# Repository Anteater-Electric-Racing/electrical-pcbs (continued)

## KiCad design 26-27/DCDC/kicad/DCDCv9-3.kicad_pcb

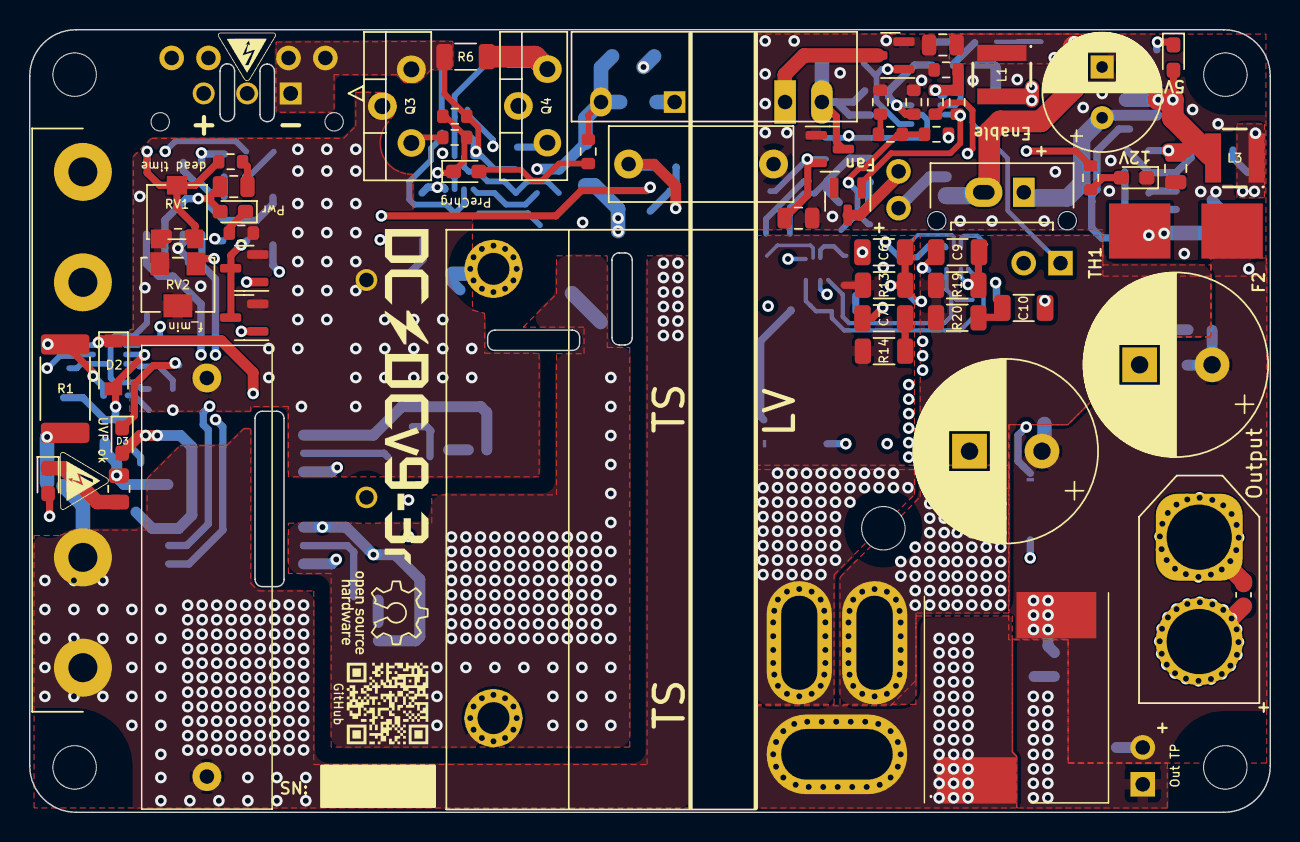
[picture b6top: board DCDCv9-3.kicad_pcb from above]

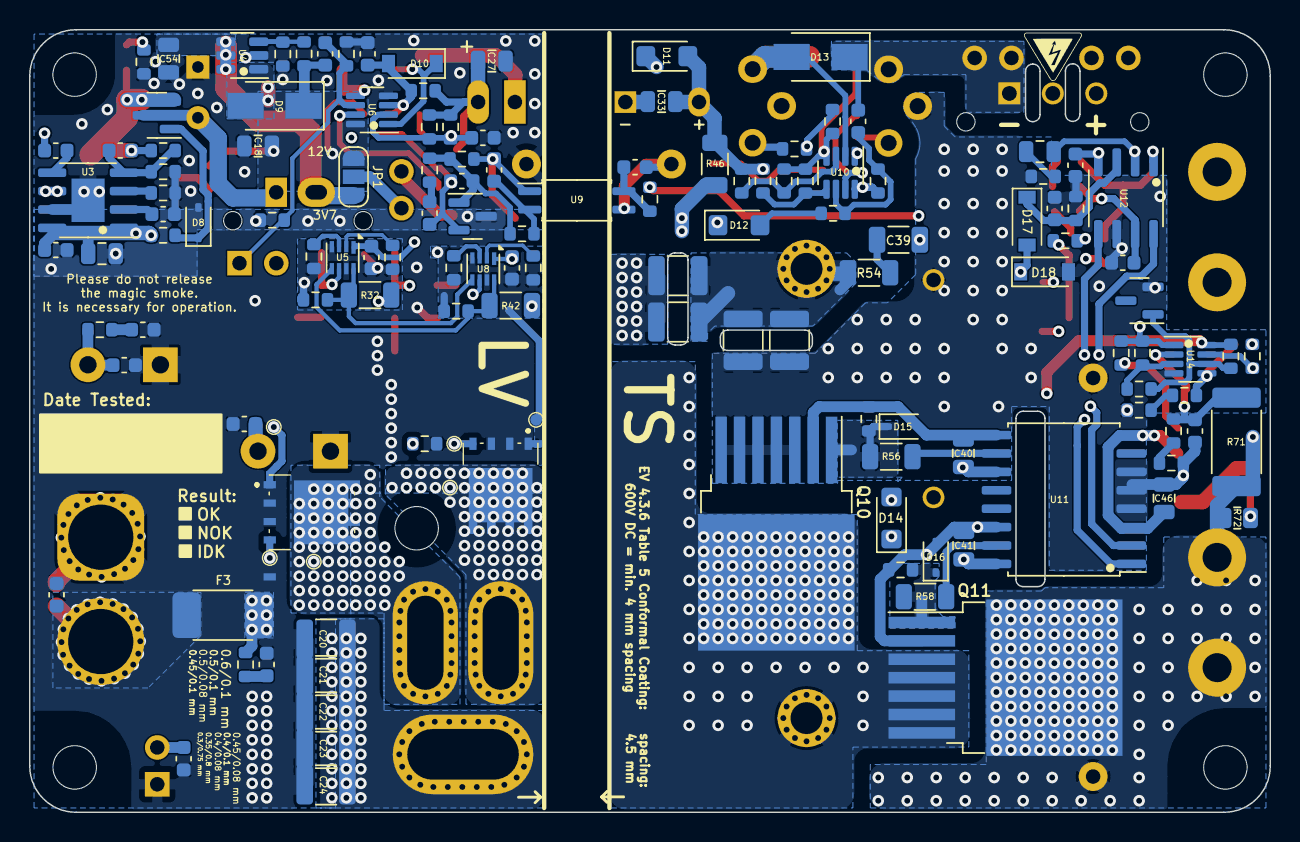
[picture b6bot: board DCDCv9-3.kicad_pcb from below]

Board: 4 copper layers, 85.6 x 54.0 mm, 208 parts (140 on the bottom side), 102 nets.

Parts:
C1: 2uF; MKP1848520704K2
C2, C15, C40, C41: 2.2uF; C_0805_2012Metric
C3: 22nF; R76UI22205050J
C4: 3.3nF; C_Disc_D12.5mm_W5.0mm_P10.00mm
C5, C33, C46: 10uF; C_0805_2012Metric
C6, C9: 1 nF; C_1206_3216Metric
C7, C10, C39: 470pF; C_1206_3216Metric
C8, C12, C18, C27, C42, C54: 22uF; C_0805_2012Metric
C11, C13: 2200uF; CP_Radial_D12.5mm_P5.00mm_symbol_inside
C14, C28: 100nF; C_0603_1608Metric
C16, C49, C50, C51, C52, C53, C55, C56, C57: 1nF; C_0603_1608Metric
C17, C19, C25, C31, C45: 1uF; C_0603_1608Metric
C20, C21, C22, C23, C24: 10uF; C_1210_3225Metric
C26, C44, C47: 22nF; C_0603_1608Metric
C29: 47pF; C_0603_1608Metric
C30, C32, C48: 10nF; C_0603_1608Metric
C34, C35, C36, C37: 5.6nF; C_1210_3225Metric
C38: 120pF; C_0603_1608Metric
C43: 470nF; C_0603_1608Metric
C_start1: 3.8V 25F Supercap; CP_Radial_D8.0mm_P3.50mm
D1: HV_Orange; LED_0603_1608Metric_Pad1.05x0.95mm_HandSolder
D2, D10, D17, D18: 1N4448; D_SOD-123
D3, D4, D5, D6, D7: Green; LED_0603_1608Metric_Pad1.05x0.95mm_HandSolder
D8, D15, D16: CDSOD323-T12; D_SOD-323
D9, D13: SS1H10; D_SMA
D11, D12, D14: VS-E7FX0212-M3/I; D_SMF
F1: 1.6A; Fuseholder0,25Zoll_32mm_littlefuse_102_122
F2: 500mA; NANO-0154-OMNI-BLOK-Fuse-Holder
F3: 20A; Bel_SMCF_Fuse_2410_6125Metric
HV_Logo_1, HV_Logo_1#2, HV_Logo_1#3: HV_Logo_1; HV_Logo_small
J1: 43650-0315; 43650-03YY_151617
J2, J4, J6, J7, J8: Conn_01x02_Male; PinHeader_1x02_P2.54mm_Vertical
J3: Conn_01x02; Molex_Micro-Fit_3.0_43650-0215_1x02_P3.00mm_Vertical_combin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
J5: XT60 Male; AMASS_XT60-F_1x02_P7.20mm_Vertical
JP1: Fan Voltage Select; SolderJumper-3_P1.3mm_Open_RoundedPad1.0x1.5mm_NumberLabels
L1: 4.7uH; ASPI-4030S
L2: 1uH; 7443091100_v9.2
L3: 10uH; ASPI-4030S
NT1, NT2: NetTie_2; dummy_net_line_0.5mm
Q1, Q2, Q5, Q6, Q7: PMV20ENR; SOT-23
Q3: SIHP24N80AE-GE3; TO-220-3_Vertical_HV1.2mm
Q4: IXYP8N90C3; TO-220-3_Vertical_HV1.2mm
Q8, Q9: BSC027N06LS5ATMA1
Q10, Q11: IMBG65R050M2HXTMA1; TO-263-7_TabPin8
QR_Coode_1: QR_Coode; GitHub_QR_Code
R1, R71: 100M; R_2512_6332Metric_Pad1.40x3.35mm_HandSolder
R2, R72: 330k; R_0805_2012Metric
R3: 3.0k; R_0603_1608Metric
R4, R39, R41, R59, R61: 1k; R_0603_1608Metric
R5, R7, R9, R11, R15, R16, R21, R23, R30, R33, R40, R43, R51, R52, R55, R57, R63: 10k; R_0603_1608Metric
R6, R14, R20: 47; R_1206_3216Metric
R8, R10, R22, R29, R38, R48, R49: 2.2k; R_0603_1608Metric
R12: 910; R_0603_1608Metric
R13, R19: 100; R_1206_3216Metric
R17, R24: 27k; R_0603_1608Metric
R18, R27, R50: 470k; R_0603_1608Metric
R25: 240k; R_0603_1608Metric
R26, R45, R47, R53, R67, R70, R75: 100k; R_0603_1608Metric
R28, R34, R66: 33k; R_0603_1608Metric
R31, R36: 4.7k; R_0603_1608Metric
R32, R42: 4.7; R_1206_3216Metric
R35: 330k; R_0603_1608Metric
R37: 47k; R_0603_1608Metric
R44: 510; R_0603_1608Metric
R46: 20; R_1206_3216Metric
R54: 10M; R_1206_3216Metric
R56, R58: 10; R_1206_3216Metric
R60: 82k; R_0603_1608Metric
R62, R69: 100M; R_0603_1608Metric
R64: 820k; R_0603_1608Metric
R65: 510k; R_0603_1608Metric
R68: 1.6M; R_0603_1608Metric
R73, R74: 10; R_0603_1608Metric
RV1: 20k; Potentiometer_Bourns_PVG3G
RV2: 10k; Potentiometer_Bourns_3214W_Vertical
T1: DIY Transformer ETD 39; Transformer_ETD39_uprightV3.6 (PSS 24V)
TH2: 1k PTC; R_0603_1608Metric
TP1, TP2, TP3, TP4, TP5, TP6: TestPoint; TestPoint_Pad_D0.8mm_DC-DC
TP8: GaN GND2; TestPoint_Pad_D0.8mm_DC-DC
U1: RP-1212S; Converter_DCDC_TRACO_TBA 1-1212HI-3kV-iso
U2: RT9058-90GVL; SOT-23
U3: MP4541_SOP8-EP; SOIC-8-1EP_3.9x4.9mm_P1.27mm_EP2.29x3mm XL7005
U4: TLV61048DBVR; SOT-23-6
U5, U8: NCP4305DMTTWG; WDFN-8_2x2mm_P0.5mm
U6, U10, U14: LM2904BIDDFR; SOT-23-8_DC-DC_v9
U7: TL431BCDBZR; SOT-23
U9: ACPL-217-50AE; SOIC-4_4.55x2.6mm_P1.27mm
U11: UCC21520DW; SOIC-16W_7.5x10.3mm_P1.27mm
U12: UCC25600; SOIC-8_3.9x4.9mm_P1.27mm
U13: ZXRE330ASA-7; SOT-23

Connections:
24V_TP: C11.1, C13.1, C50.2, C51.2, C52.2, F2.1, F3.1, J4.1, L2.2, R17.1, R73.1, R74.1
+3V7: C8.1, C54.1, J3.2, JP1.3 (B), L1.1, U4.4 (~SHDN), U4.5 (IN), U4.6 (nc)
+9V: C5.1, C30.2, R39.1, U2.2 (VO), U9.1
+12V_HS: C41.2, D14.1 (K), U11.16 (VDDA)
+12V_IN: C2.2, C40.2, C45.2, C46.1, D2.1 (K), D3.2 (A), D4.2 (A), D11.1 (K), R70.1, U11.3 (VCCI), U11.8 (VCCI), U11.11 (VDDB), U12.7 (VCC), U14.8 (V+)
+12V_sw: C18.1, C19.2, C25.1, C27.1, C31.1, D9.1 (K), J8.1, JP1.1 (A), R16.1, R21.2, R27.1, R34.1, R35.2, R36.2, U1.1 (+VIN), U2.3 (VI), U5.1 (VCC), U6.8 (V+), U8.1 (VCC)
+24V: C15.2, C53.2, F2.2, R26.2, U3.1 (EN), U3.8 (VIN)
+HV: C1.2, C34.1, C35.1, F1.2, Q11.8 (D), R1.1, R71.1, R72.1
+HV_in: F1.1, J1.3, J7.1, J7.2
-HV_in: C33.2, C38.1, D13.1 (K), J1.1, J6.1, J6.2, Q3.3 (S), R6.2, R7.2, R48.1, R50.1, R51.2, U1.5 (-VOUT), U10.4 (V-)
-HV_pc: C1.1, C3.2, C4.1, C32.2, C36.2, C37.2, C43.2, C44.1, C45.1, C46.2, C47.2, D12.1 (K), D18.2 (A), Q1.2 (S), Q2.2 (S), Q3.2 (D), Q4.2 (C), Q10.3 (S), Q10.4 (S), Q10.5 (S), Q10.6 (S), Q10.7 (S), R2.2, R3.2, R5.1, R59.2, R60.1, R65.2, R68.2, RV1.3, RV2.2, RV2.3, U9.3, U11.4 (GND), U11.5 (DIS), U11.6 (DT), U12.6 (GND), U13.2, U14.4 (V-)
/HB_out: Q10.8 (D), Q11.3 (S), Q11.4 (S), Q11.5 (S), Q11.6 (S), Q11.7 (S), T1.1 (AA)
/HS: U11.1 (INA), U12.8 (GD1)
/LS: U11.2 (INB), U12.5 (GD2)
/OC: C44.2, D17.1 (K), R60.2, U12.3 (OC)
/OTP_FAN: Q5.1 (G), R18.1, U6.7
/OTP_OFF: D10.1 (K), Q6.1 (G), U6.1
/OVP: Q2.1 (G), R69.1, U14.7
/Opc+: C32.1, R44.2, U9.4
/Synchronous Rectification/3: Q9.5 (D_1), Q9.6 (D_2), Q9.7 (D_3), Q9.8 (D_4), Q9.9 (D_5), R13.2, R14.1, T1.3 (SB), TP5.1
/Synchronous Rectification/5: Q8.5 (D_1), Q8.6 (D_2), Q8.7 (D_3), Q8.8 (D_4), Q8.9 (D_5), R19.2, R20.1, T1.5 (SA), TP3.1
/UVP: Q1.1 (G), R62.1, R63.1, U14.1
GND: C4.2, C5.2, C7.1, C8.2, C10.1, C11.2, C12.1, C13.2, C15.1, C17.1, C18.2, C20.2, C21.2, C22.2, C23.2, C24.2, C27.2, C28.1, C48.1, C49.1, C50.1, C51.1, C52.1, C53.1, C54.2, C55.1, C56.1, C57.1, C_start1.2 (-), D6.1 (K), D8.2 (A2), J4.2, J5.2, NT1.2, NT2.2, Q5.2 (S), Q6.2 (S), Q8.1 (S_1), Q8.2 (S_2), Q8.3 (S_3), Q9.1 (S_1), Q9.2 (S_2), Q9.3 (S_3), R10.2, R11.2, R15.1, R22.1, R23.2, R25.1, R28.2, R31.1, R75.2, TH2.2, TP8.1, U2.1 (GND), U3.7 (GND), U4.2 (GND), U6.4 (V-), U7.3 (A)
unnamed: C2.1, R4.2
unnamed: C7.2, R14.2
unnamed: C10.2, R20.2
unnamed: C26.2, R37.1
unnamed: C30.1, R41.1, U9.2
unnamed: C39.2, R54.1
unnamed: C42.2, R59.1
unnamed: C56.2, R73.2
unnamed: C57.2, R74.2
unnamed: C_start1.1 (+), J3.1, Q7.3 (D)
unnamed: D1.2 (A), R72.2
unnamed: D1.1 (K), R2.1
unnamed: C47.1, D2.2 (A), R67.2, R71.2, U14.2 (-)
unnamed: D3.1 (K), R63.2
unnamed: D4.1 (K), R5.2
unnamed: D5.2 (A), R9.1
unnamed: D5.1 (K), R7.1, R8.2, U10.7
unnamed: D6.2 (A), R21.1
unnamed: C12.2, C16.2, D7.2 (A), L3.2, Q7.2 (S), R24.1
unnamed: D7.1 (K), R22.2
unnamed: D8.1 (A1), Q7.1 (G), R26.1
unnamed: D9.2 (A), L1.2, U4.1 (SW)
unnamed: C48.2, D10.2 (A), R11.1, R34.2, U6.3 (+)
unnamed: C33.1, D11.2 (A), R9.2, R45.2, R46.2, R47.2, R53.2, U1.7 (+VOUT), U10.8 (V+)
unnamed: D12.2 (A), R52.1
unnamed: D13.2 (A), Q4.3 (E), R6.1, U10.2 (-)
unnamed: D14.2 (A), R46.1
unnamed: D15.1 (A1), Q10.1 (G), R55.1, R56.1
unnamed: C40.1, D15.2 (A2), Q10.2 (DS), R55.2, U11.9 (VSSB)
unnamed: D16.1 (A1), Q11.1 (G), R57.1, R58.1
unnamed: C41.1, D16.2 (A2), Q11.2 (DS), R57.2, U11.14 (VSSA)
unnamed: C39.1, D17.2 (A), D18.1 (K)
unnamed: J2.1, JP1.2 (C)
unnamed: J2.2, Q5.3 (D)
unnamed: C49.2, C55.2, F3.2, J5.1
unnamed: C19.1, J8.2, R31.2, R75.1, U6.6 (-)
unnamed: Q1.3 (D), Q2.3 (D), R61.1
unnamed: Q3.1 (G), R8.1
unnamed: Q4.1 (G), R49.1
unnamed: Q8.4 (G), R32.1, TP2.1
unnamed: Q9.4 (G), R42.1, TP4.1
unnamed: R10.1, R12.2
unnamed: R49.2, R51.1, U10.1
unnamed: R65.1, R66.2
unnamed: R67.1, R68.1
unnamed: C34.2, C35.2, C36.1, C37.1, R54.2, T1.2 (AB)
unnamed: C20.1, C21.1, C22.1, C23.1, C24.1, L2.1, T1.4 (SC)
unnamed: C14.2, U3.5 (BST)
unnamed: C16.1, R23.1, R24.2, U3.4 (FB)
unnamed: R25.2, U3.3 (FREQU)
unnamed: C14.1, L3.1, U3.6 (SW)
unnamed: C17.2, U3.2 (VCC)
unnamed: R27.2, R28.1, U4.3 (FB)
unnamed: C9.2, R19.1, U5.6 (CS)
unnamed: R30.2, R32.2, U5.8 (DRV), U8.5 (TRIG/DIS)
unnamed: C9.1, C25.2, NT1.1, R29.1, R30.1, R33.1, TP1.1, U5.4 (LLD), U5.7 (GND)
unnamed: R33.2, U5.2 (MIN_TOFF)
unnamed: R29.2, U5.3 (MIN_TON)
unnamed: R40.2, R42.2, U5.5 (TRIG/DIS), U8.8 (DRV)
unnamed: C28.2, R35.1, R36.1, TH2.1, U6.2 (-)
unnamed: R15.2, R16.2, R18.2, U6.5 (+)
unnamed: C29.2, R37.2, R39.2, R41.2, U7.1 (K)
unnamed: C26.1, C29.1, R12.1, R17.2, U7.2 (REF)
unnamed: C6.2, R13.1, U8.6 (CS)
unnamed: C6.1, C31.2, NT2.1, R38.1, R40.1, R43.1, TP6.1, U8.4 (LLD), U8.7 (GND)
unnamed: R43.2, U8.2 (MIN_TOFF)
unnamed: R38.2, U8.3 (MIN_TON)
unnamed: R45.1, R48.2, U10.3 (+)
unnamed: R47.1, R50.2, U10.5 (+)
unnamed: C38.2, R52.2, R53.1, U10.6 (-)
unnamed: R58.2, U11.15 (OUTA)
unnamed: R56.2, U11.10 (OUTB)
unnamed: R3.1, R4.1, RV1.1, RV1.2, U12.1 (DT)
unnamed: C42.1, R44.1, RV2.1, U12.2 (RT)
unnamed: C43.1, R61.2, U12.4 (SS)
unnamed: R62.2, R64.1, U14.3 (+)
unnamed: R1.2, R66.1, R69.2, U14.5 (+)
unnamed: R64.2, R70.2, U13.1, U14.6 (-)
OTP_FET: Q6.3 (D), U1.2 (-VIN)

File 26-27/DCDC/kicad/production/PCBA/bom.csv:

Designator,Footprint,Quantity,Value,LCSC Part #
C1,MKP1848520704K2,1,2uF,
"C11, C13",CP_Radial_D12.5mm_P5.00mm_symbol_inside,2,2200uF,
"C12, C18, C27, C42, C54, C8",0805,6,22uF,
"C14, C28",0603,2,100nF,
"C15, C40, C41",0805,3,2.2uF,
"C16, C49, C50, C51, C52, C53, C56, C57",0603,8,1nF,
"C17, C19, C25, C31, C45",0603,5,1uF,
"C20, C21, C22, C23, C24",1210,5,10uF,
"C26, C44, C47",0603,3,22nF,
C29,0603,1,47pF,
"C30, C32, C48",0603,3,10nF,
"C33, C46, C5",0805,3,10uF,
"C34, C35, C36, C37",1210,4,5.6nF,
C39,1206,1,470pF,
C4,C_Disc_D12.5mm_W5.0mm_P10.00mm,1,3.3nF,
C43,0603,1,470nF,
"C6, C9",1206,2,1 nF,
C_START1,CP_Radial_D8.0mm_P3.50mm,1,3.8V 25F Supercap,
D1,0603,1,HV_Orange,
"D10, D17, D18, D2",D_SOD-123,4,1N4448,
"D11, D12, D14",D_SMF,3,VS-E7FX0212-M3/I,
"D13, D9",D_SMA,2,SS1H10,
"D15, D16, D8",D_SOD-323,3,CDSOD323-T12,
"D3, D4, D5, D6, D7",0603,5,Green,
F1,"Fuseholder0,25Zoll_32mm_littlefuse_102_122",1,1.6A,
F2,NANO-0154-OMNI-BLOK-Fuse-Holder,1,500mA,
F3,Bel_SMCF_Fuse_2410_6125Metric,1,20A,
J1,43650-03YY_151617,1,43650-0315,
"J2, J4, J8",PinHeader_1x02_P2.54mm_Vertical,3,Conn_01x02_Male,
J3,Molex_Micro-Fit_3.0_43650-0215_1x02_P3.00mm_Vertical_combined2.54pinheader,1,Conn_01x02,
J5,AMASS_XT60-F_1x02_P7.20mm_Vertical,1,XT60 Male,
JP1,SolderJumper-3_P1.3mm_Open_RoundedPad1.0x1.5mm_NumberLabels,1,Fan Voltage Select,
L1,ASPI-4030S,1,4.7uH,
L2,7443091100_v9.2,1,1uH,
L3,ASPI-4030S,1,10uH,
"Q1, Q2, Q5, Q6, Q7",SOT-23,5,PMV20ENR,
"Q10, Q11",TO-263-7_TabPin8,2,IMBG65R050M2HXTMA1,
Q3,TO-220-3_Vertical_HV1.2mm,1,SIHP24N80AE-GE3,
Q4,TO-220-3_Vertical_HV1.2mm,1,IXYP8N90C3,
"Q8, Q9",BSC027N06LS5ATMA1,2,BSC027N06LS5ATMA1,
"R1, R71",2512,2,100M,
"R10, R22, R29, R38, R48, R49, R8",0603,7,2.2k,
"R11, R15, R16, R21, R23, R30, R33, R40, R43, R5, R51, R52, R55, R57, R63, R7, R9",0603,17,10k,
R12,0603,1,910,
"R13, R19",1206,2,100,
"R17, R24",0603,2,27k,
"R18, R27, R50",0603,3,470k,
"R2, R72",0805,2,330k,
R25,0603,1,240k,
"R26, R45, R47, R53, R67, R70, R75",0603,7,100k,
"R28, R34, R66",0603,3,33k,
"R31, R36",0603,2,4.7k,
"R32, R42",1206,2,4.7,
R35,0603,1,330k,
R37,0603,1,47k,
"R39, R41, R59, R61",0603,4,1k,
R44,0603,1,510,
R46,1206,1,20,
R54,1206,1,10M,
"R56, R58",1206,2,10,
R6,1206,1,47,
R60,0603,1,82k,
"R62, R69",0603,2,100M,
R64,0603,1,820k,
R65,0603,1,510k,
R68,0603,1,1.6M,
"R73, R74",0603,2,10,
RV1,Potentiometer_Bourns_PVG3G,1,20k,
RV2,Potentiometer_Bourns_3214W_Vertical,1,10k,
T1,Transformer_ETD39_uprightV3.6 (PSS 24V),1,DIY Transformer ETD 39,
TH2,0603,1,1k PTC,
U1,Converter_DCDC_TRACO_TBA 1-1212HI-3kV-iso,1,RP-1212S,
"U10, U14, U6",SOT-23-8_DC-DC_v9,3,LM2904BIDDFR,
U11,SOIC-16W_7.5x10.3mm_P1.27mm,1,UCC21520DW,
U12,SOIC-8_3.9x4.9mm_P1.27mm,1,UCC25600,
U13,SOT-23,1,ZXRE330ASA-7,
U2,SOT-23,1,RT9058-90GVL,
U3,SOIC-8-1EP_3.9x4.9mm_P1.27mm_EP2.29x3mm XL7005,1,MP4541_SOP8-EP,
U4,SOT-23-6,1,TLV61048DBVR,
"U5, U8",WDFN-8_2x2mm_P0.5mm,2,NCP4305DMTTWG,
U7,SOT-23,1,TL431BCDBZR,
U9,SOIC-4_4.55x2.6mm_P1.27mm,1,ACPL-217-50AE,

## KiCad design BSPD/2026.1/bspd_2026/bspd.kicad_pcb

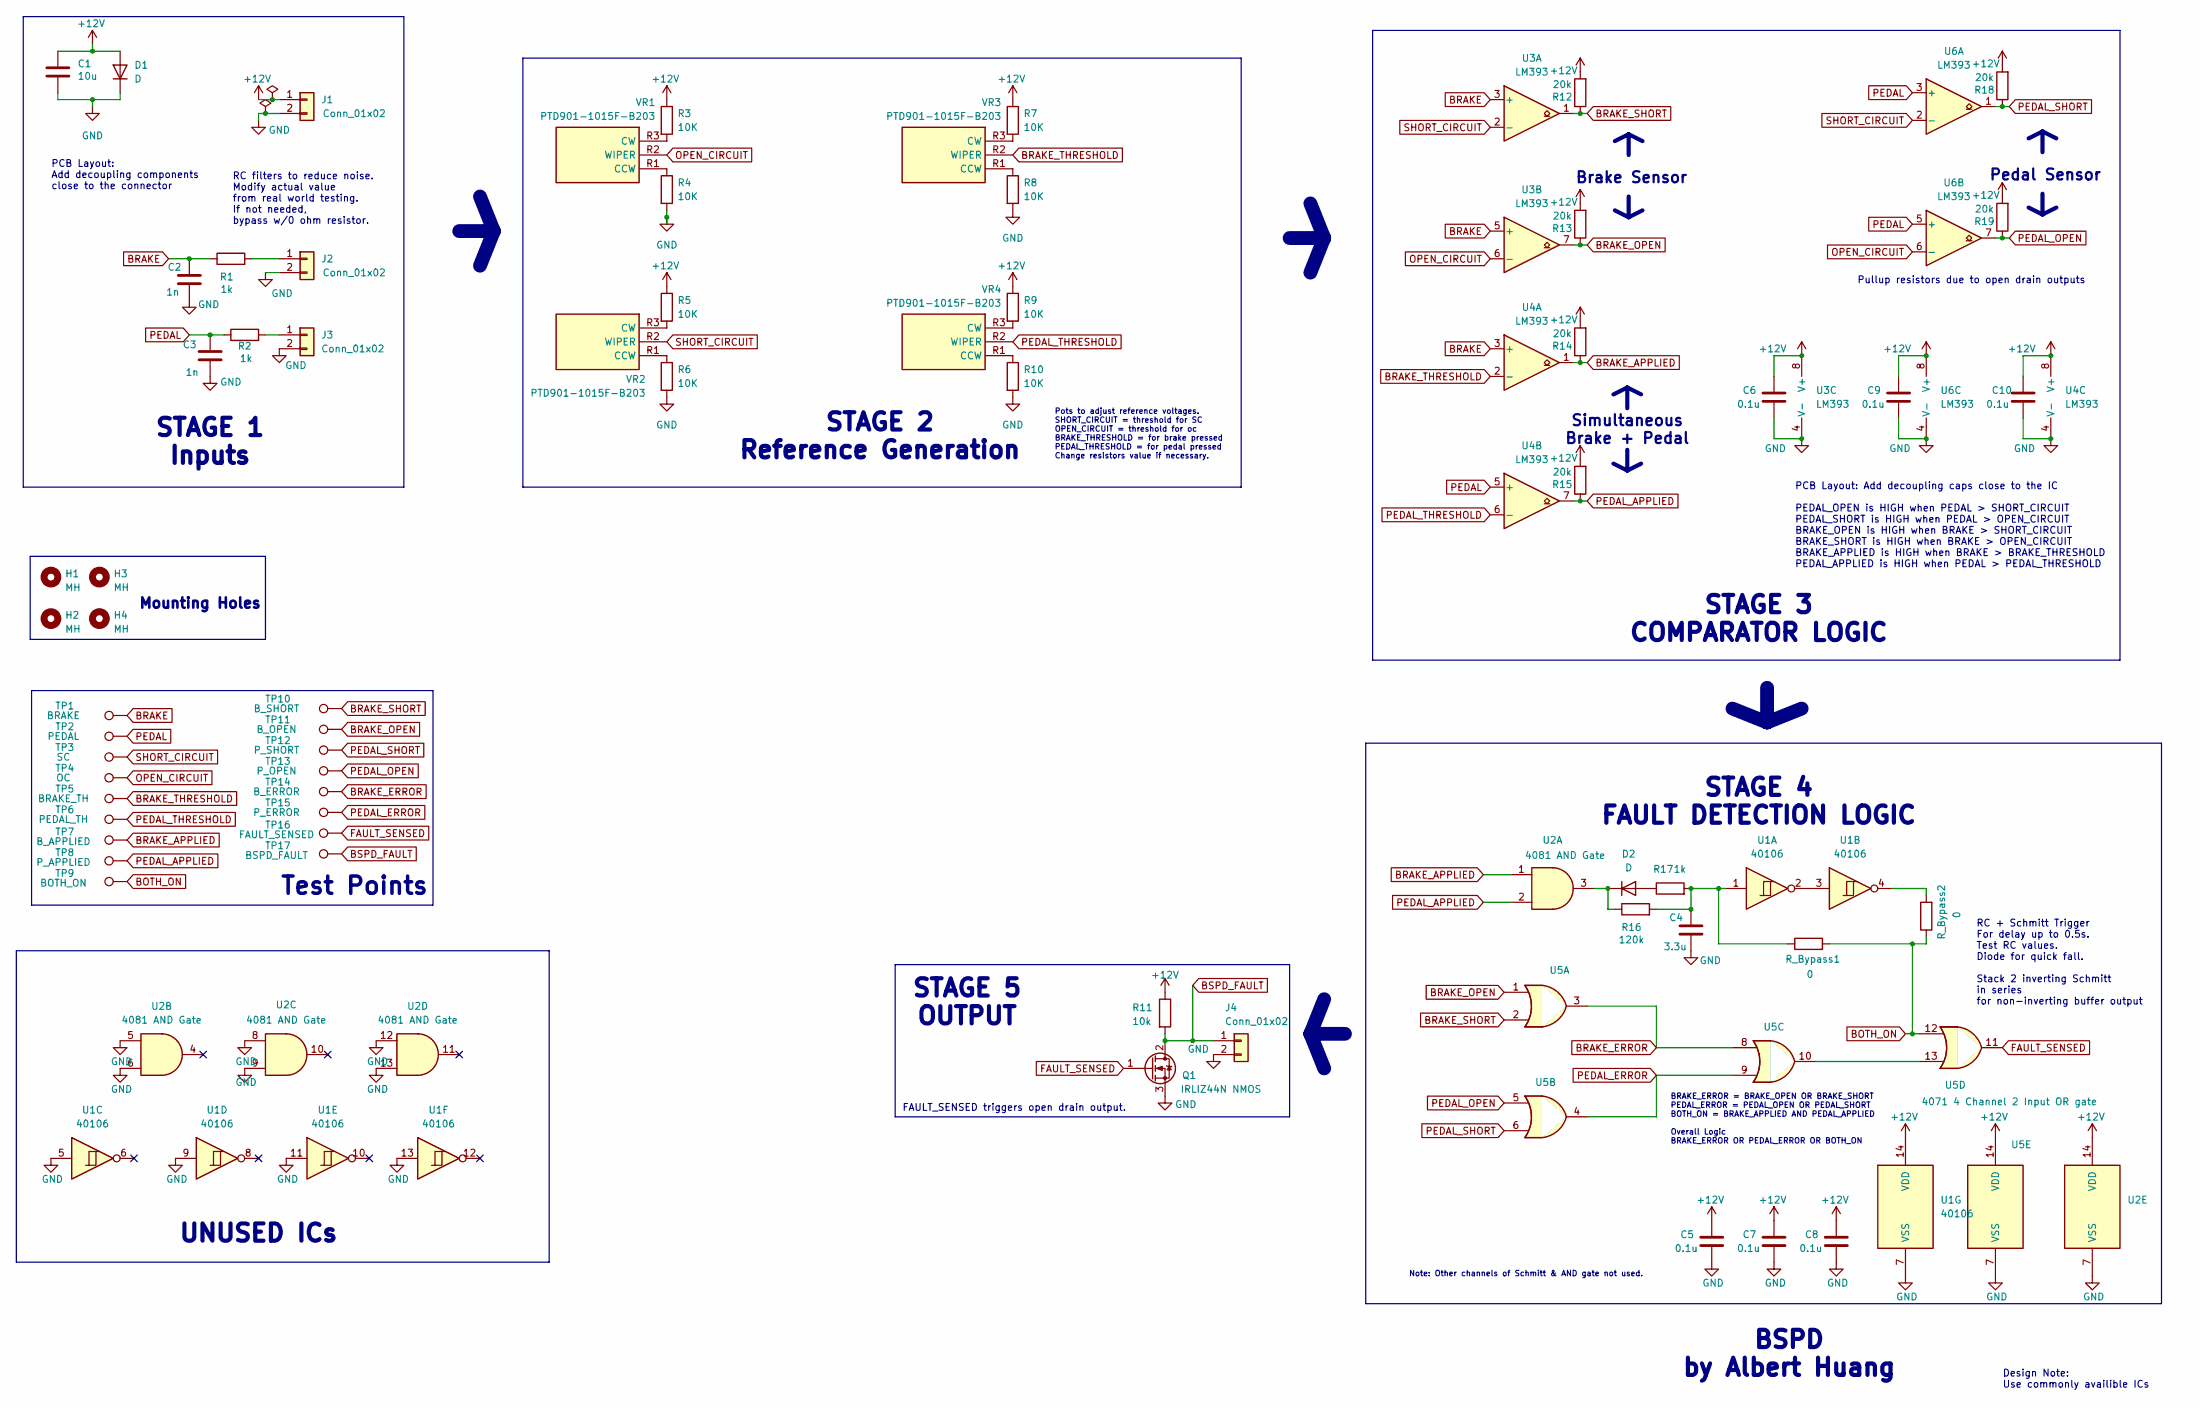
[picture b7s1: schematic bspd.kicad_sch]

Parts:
C1: 10u; C_0603_1608Metric
C2, C3: 1n; C_0603_1608Metric
C4: 3.3u; C_0603_1608Metric
C5, C6, C7, C8, C9, C10: 0.1u; C_0603_1608Metric
D1, D2: D; D_0603_1608Metric
H1, H2, H3, H4: MH; MountingHole_3mm
J1, J2, J3, J4: Conn_01x02; Molex_CLIK-Mate_502382-0270_1x02-1MP_P1.25mm_Vertical
Q1: IRLIZ44N NMOS; TO-220F-3_Vertical
R1, R2, R17: 1k; R_0603_1608Metric
R3, R4, R5, R6, R7, R8, R9, R10: 10K; R_0603_1608Metric
R11: 10k; R_0603_1608Metric
R12, R13, R14, R15, R18, R19: 20k; R_0603_1608Metric
R16: 120k; R_0603_1608Metric
R_Bypass1, R_Bypass2: 0; R_0603_1608Metric
TP1: BRAKE; TestPoint_Pad_D2.5mm
TP2: PEDAL; TestPoint_Pad_D2.5mm
TP3: SC; TestPoint_Pad_D2.5mm
TP4: OC; TestPoint_Pad_D2.5mm
TP5: BRAKE_TH; TestPoint_Pad_D2.5mm
TP6: PEDAL_TH; TestPoint_Pad_D2.5mm
TP7: B_APPLIED; TestPoint_Pad_D2.5mm
TP8: P_APPLIED; TestPoint_Pad_D2.5mm
TP9: BOTH_ON; TestPoint_Pad_D2.5mm
TP10: B_SHORT; TestPoint_Pad_D2.5mm
TP11: B_OPEN; TestPoint_Pad_D2.5mm
TP12: P_SHORT; TestPoint_Pad_D2.5mm
TP13: P_OPEN; TestPoint_Pad_D2.5mm
TP14: B_ERROR; TestPoint_Pad_D2.5mm
TP15: P_ERROR; TestPoint_Pad_D2.5mm
TP16: FAULT_SENSED; TestPoint_Pad_D2.5mm
TP17: BSPD_FAULT; TestPoint_Pad_D2.5mm
U1: 40106; DIP-14_W7.62mm_Socket
U2: 4081 AND Gate; DIP-14_W7.62mm_Socket
U3, U4, U6: LM393; DIP-8_W7.62mm_Socket
U5: 4071 4 Channel 2 Input OR gate; DIP-14_W7.62mm_Socket
VR1, VR2, VR3, VR4: PTD901-1015F-B203; PTD9011015FB203; Mouser Part Number 652-PTD901-1015FB203

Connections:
+12V: C1.1, C5.1, C6.1, C7.1, C8.1, C9.1, C10.1, D1.2 (A), J1.1, R3.1, R5.1, R7.1, R9.1, R11.1, R12.2, R13.2, R14.2, R15.2, R18.2, R19.2, U1.14 (VDD), U2.14 (VDD), U3.8 (V+), U4.8 (V+), U5.14 (VDD), U6.8 (V+)
BOTH_ON: R_Bypass1.2, R_Bypass2.1, TP9.1, U5.12
BRAKE: C2.1, R1.1, TP1.1, U3.3 (+), U3.5 (+), U4.3 (+)
BRAKE_APPLIED: R14.1, TP7.1, U2.1, U4.1
BRAKE_ERROR: TP14.1, U5.3, U5.8
BRAKE_OPEN: R13.1, TP11.1, U3.7, U5.1
BRAKE_SHORT: R12.1, TP10.1, U3.1, U5.2
BRAKE_THRESHOLD: TP5.1, U4.2 (-), VR3.R2 (WIPER)
BSPD_FAULT: J4.1, Q1.2 (D), R11.2, TP17.1
FAULT_SENSED: Q1.1 (G), TP16.1, U5.11
GND: C1.2, C2.2, C3.2, C4.2, C5.2, C6.2, C7.2, C8.2, C9.2, C10.2, D1.1 (K), J1.2, J2.2, J3.2, J4.2, Q1.3 (S), R4.2, R6.2, R8.2, R10.2, U1.5, U1.7 (VSS), U1.9, U1.11, U1.13, U2.5, U2.6, U2.7 (VSS), U2.8, U2.9, U2.12, U2.13, U3.4 (V-), U4.4 (V-), U5.7 (VSS), U6.4 (V-)
unnamed: C4.1, R16.2, R17.2, R_Bypass1.1, U1.1
unnamed: D2.2 (A), R17.1
unnamed: D2.1 (K), R16.1, U2.3
unnamed: J2.1, R1.2
unnamed: J3.1, R2.2
unnamed: R_Bypass2.2, U1.4
unnamed: U1.2, U1.3
unnamed: U5.10, U5.13
unnamed: R4.1, VR1.R1 (CCW)
unnamed: R3.2, VR1.R3 (CW)
unnamed: R6.1, VR2.R1 (CCW)
unnamed: R5.2, VR2.R3 (CW)
unnamed: R8.1, VR3.R1 (CCW)
unnamed: R7.2, VR3.R3 (CW)
unnamed: R10.1, VR4.R1 (CCW)
unnamed: R9.2, VR4.R3 (CW)
OPEN_CIRCUIT: TP4.1, U3.6 (-), U6.6 (-), VR1.R2 (WIPER)
PEDAL: C3.1, R2.1, TP2.1, U4.5 (+), U6.3 (+), U6.5 (+)
PEDAL_APPLIED: R15.1, TP8.1, U2.2, U4.7
PEDAL_ERROR: TP15.1, U5.4, U5.9
PEDAL_OPEN: R19.1, TP13.1, U5.5, U6.7
PEDAL_SHORT: R18.1, TP12.1, U5.6, U6.1
PEDAL_THRESHOLD: TP6.1, U4.6 (-), VR4.R2 (WIPER)
SHORT_CIRCUIT: TP3.1, U3.2 (-), U6.2 (-), VR2.R2 (WIPER)

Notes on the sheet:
STAGE 2 Reference Generation
STAGE 3 COMPARATOR LOGIC
Mounting Holes
RC filters to reduce noise. Modify actual value from real world testing. If not needed, bypass w/0 ohm resistor.
PCB Layout: Add decoupling components close to the connector
Note: Other channels of Schmitt & AND gate not used.
Pedal Sensor
STAGE 1 Inputs
UNUSED ICs
BRAKE_ERROR = BRAKE_OPEN OR BRAKE_SHORT PEDAL_ERROR = PEDAL_OPEN OR PEDAL_SHORT BOTH_ON = BRAKE_APPLIED AND PEDAL_APPLIED Overall Logic BRAKE_ERROR OR PEDAL_ERROR OR BOTH_ON
Pots to adjust reference voltages. SHORT_CIRCUIT = threshold for SC OPEN_CIRCUIT = threshold for oc BRAKE_THRESHOLD = for brake pressed PEDAL_THRESHOLD = for pedal pressed Change resistors value if necessary.
RC + Schmitt Trigger For delay up to 0.5s. Test RC values. Diode for quick fall. Stack 2 inverting Schmitt in series for non-inverting buffer output
Test Points
STAGE 4 FAULT DETECTION LOGIC
STAGE 5 OUTPUT
PCB Layout: Add decoupling caps close to the IC PEDAL_OPEN is HIGH when PEDAL > SHORT_CIRCUIT PEDAL_SHORT is HIGH when PEDAL > OPEN_CIRCUIT BRAKE_OPEN is HIGH when BRAKE > SHORT_CIRCUIT BRAKE_SHORT is HIGH when BRAKE > OPEN_CIRCUIT BRAKE_APPLIED is HIGH when BRAKE > BRAKE_THRESHOLD PEDAL_APPLIED is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
Pullup resistors due to open drain outputs
Design Note: Use commonly availible ICs
FAULT_SENSED triggers open drain output.
Brake Sensor
BSPD by Albert Huang
Simultaneous Brake + Pedal

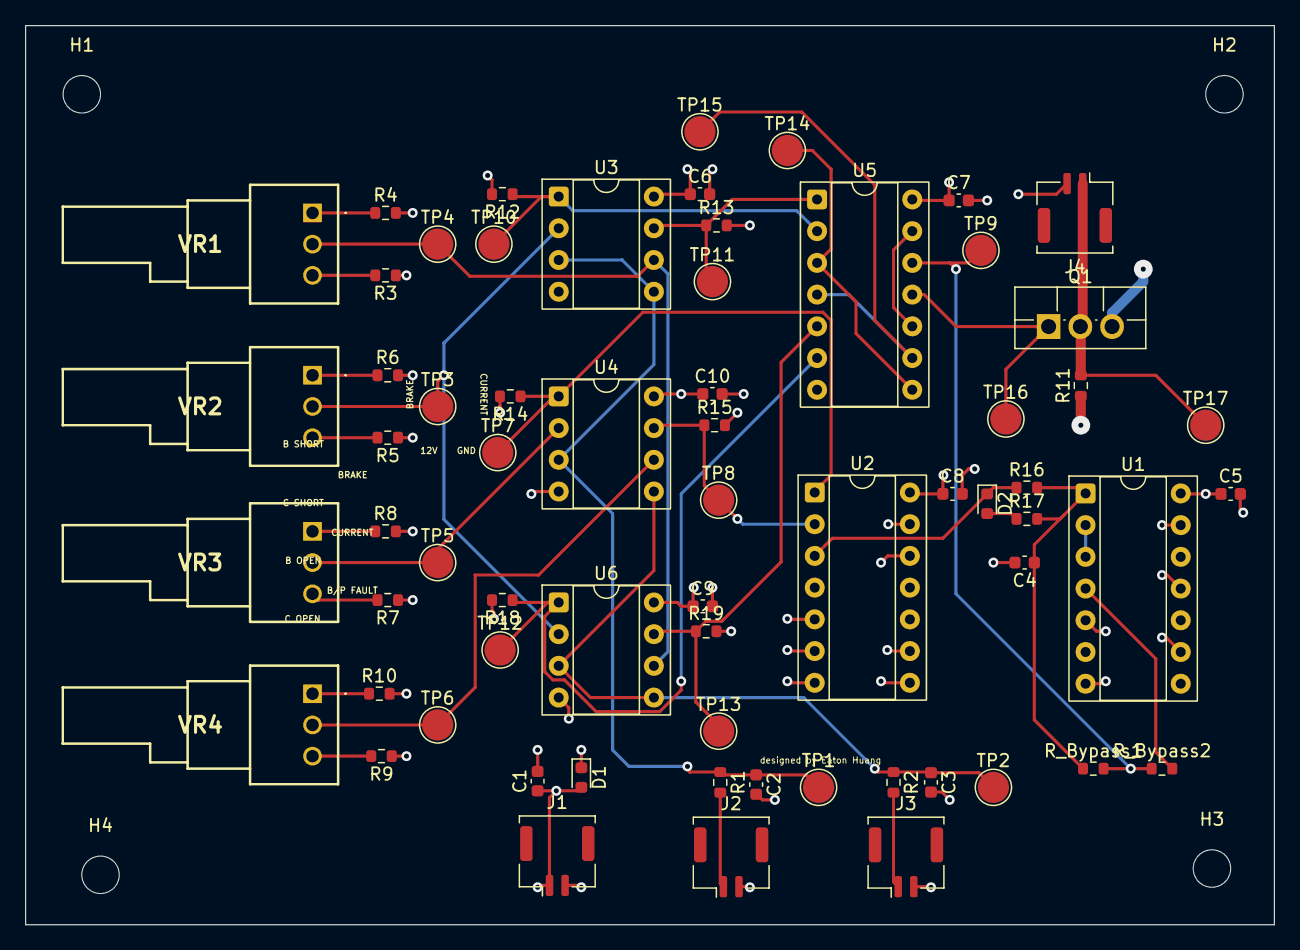
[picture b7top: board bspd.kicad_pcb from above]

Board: 4 copper layers, 100.0 x 72.0 mm, 69 parts (0 on the bottom side), 35 nets.
